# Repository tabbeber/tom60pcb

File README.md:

# Configuring PCB
To configure this PCB, head over to my [config repository](https://github.com/tabbeber/zmk-config). Follow the instructions there, and you should be set at modifying the keymap.

# About

This project is inspired by [isometria75](https://github.com/ebastler/isometria-75). 
Schematics and parts were used as a baseline, together with some information from the [nrfMicro-project](https://github.com/joric/nrfmicro/). 
Also thanks to Martin in the Norwegian mechanical keyboard discord for feedback and a slick logo to put on it.

What this project attempts to do is to fill a gap in the mid-tier of the custom mechanical keyboard market, where bluetooth/wireless boards are few and far between. 
Most of them are closed source or difficult to get hold of.
This is also mostly a project for me build skills within PCB design.
Feel free to come with any feedback - I have no clue what I'm doing.

This project was originally born out of an idea to create a PCB which was specifically made for gummyworm-mounting in regular tray mount cases without needing to massacre the poor case.
Eventually the PCB looked decent, and regular tray mount PCB would likely have a broader appeal than some hacky gummywork gasket.

# Current parts

Currently this design requires a [smaller lithium battery](https://www.aliexpress.com/item/32831998939.html), which is placed between the PCB and plate of the build.
These batteries are only 3mm tall, 30mm long and 12mm wide.
This approach is not suited for plateless builds.
Ideally uses a 2-pin JST connector, but can probably also be soldered directly to the PCB.

This PCB uses the same [Holyiot 18010](https://www.aliexpress.com/item/32868002366.html) chip that the isometria75 does. This chip comes without a bootloader, and thus need to be programmed before use.

Currently the PCB uses a forced tsangan layout for the bottom row to make space for the MCU and the battery, while the rest should be fairly universal; support for split backspace, iso and ansi.

# Current progress

Currently the project requires some more work with its footprints, but it's almost ready for prototyping. No parts are currently ordered for the future prototype.

# To-do
- [x] Make a supported layout chart
- [x] Order Battery, MCU, and Programmer for the MCU
- [x] Fix PCB and final touchups
- [x] Order PCB prototype
	* PCB rev. 0.2 has arrived
	* Current revision mostly contain cosmetic changes and improved via placements - the electrical and functional configuration remain very similar to rev. 0.2
- [x] Write and configure firmware (bootloader, ZMK)
	* ZMK firmware is functional. Currently need to figure out uploading and creating a github actions repo, as per ZMK guidelines.
- [ ] Possibly make a small wiki?

# Future possibilities

* Use of different chip(format), like the nRF52840 in the E73 format, which seem abundant on aliexpress
* Modified versions for ortho, gummyworm mount, and through-hole kits.

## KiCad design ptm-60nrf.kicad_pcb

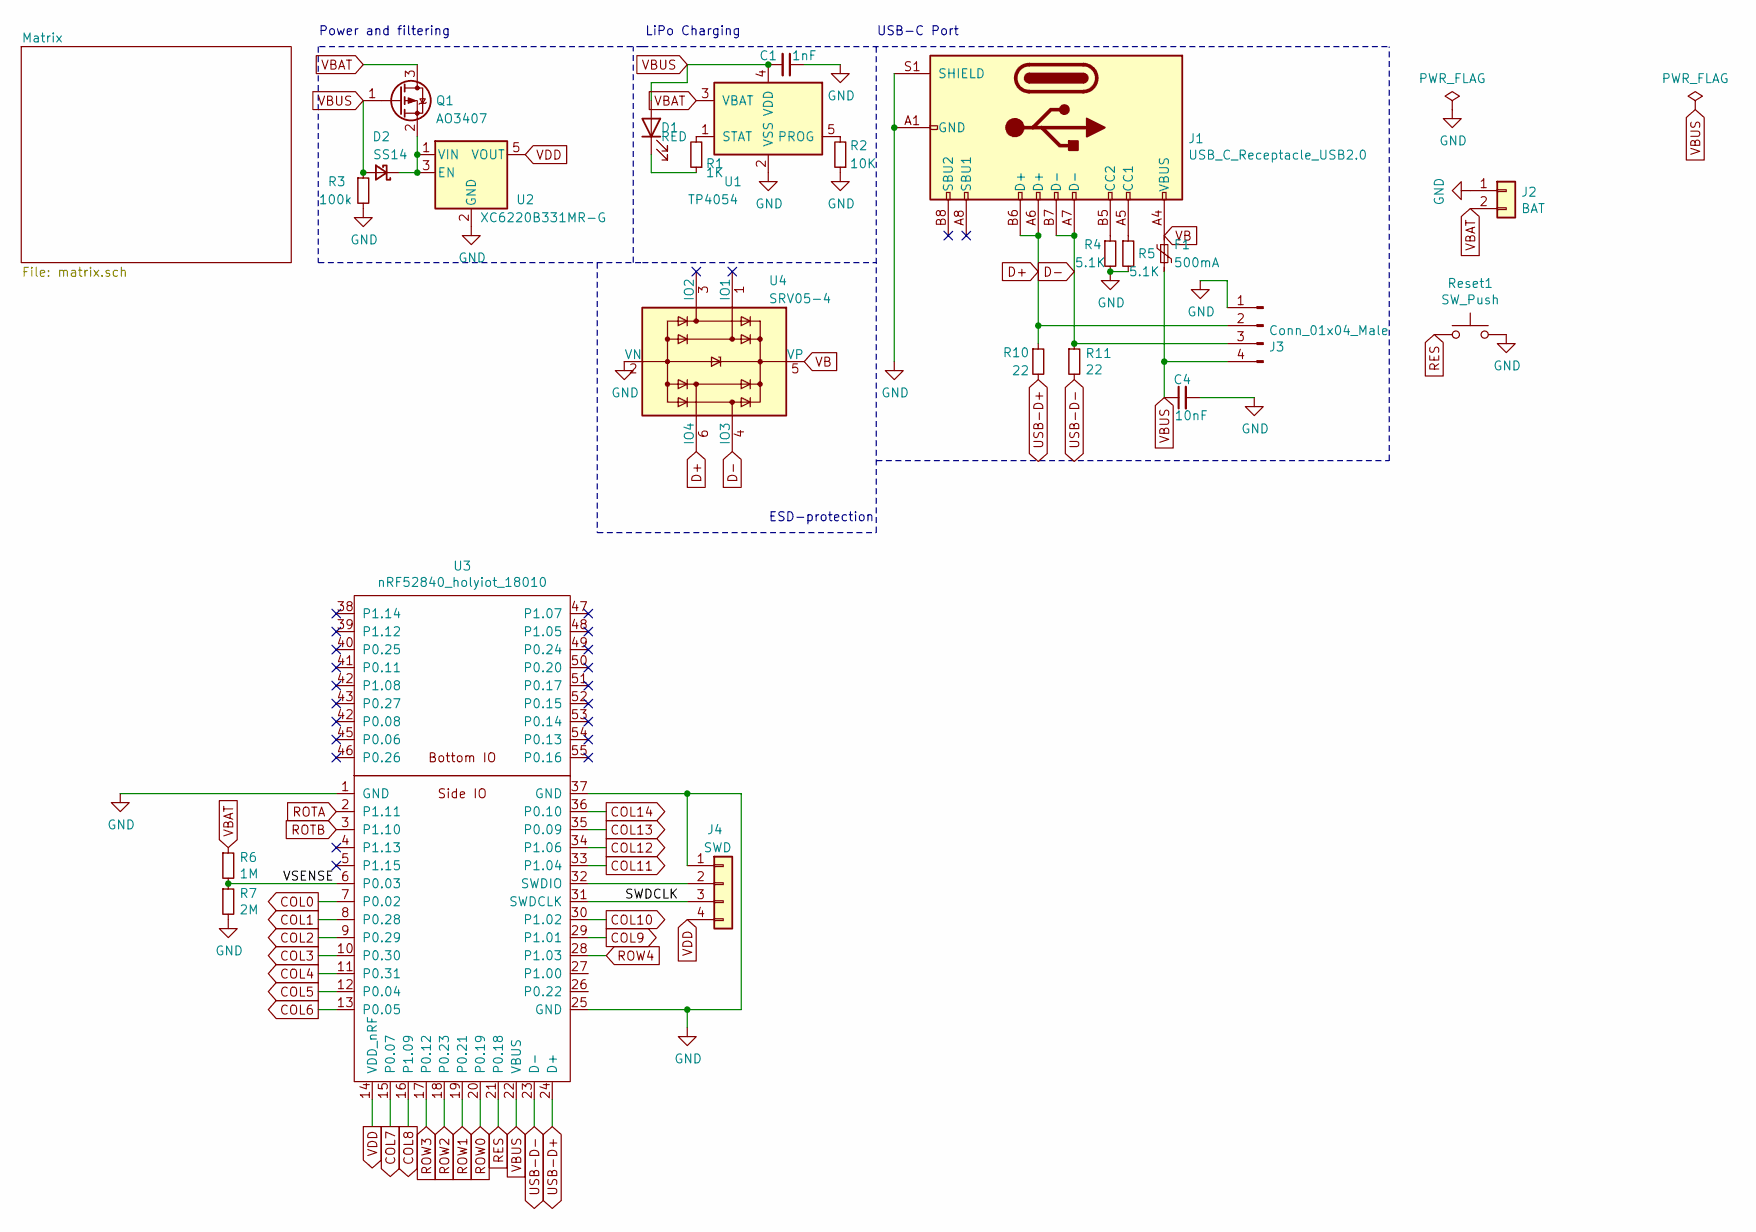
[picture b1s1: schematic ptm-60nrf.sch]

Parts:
C1: 1nF; C_0402_1005Metric; JLCPCB C1523
C4: 10nF; R_0402_1005Metric; JLCPCB C15195
D1: RED; LED_0805_2012Metric; JLCPCB C84256
D2: SS14; D_SMA; JLCPCB C2480
F1: 500mA; Fuse_1206_3216Metric; JLCPCB C70069
J1: USB_C_Receptacle_USB2.0; USB_C_Receptacle_HRO_TYPE-C-31-M-12; JLCPCB C165948
J2: BAT; JST_SH_SM02B-SRSS-TB_1x02-1MP_P1.00mm_Horizontal
J3: Conn_01x04_Male; JST_SH_BM04B-SRSS-TB_1x04-1MP_P1.00mm_Vertical
J4: SWD; PinSocket_1x04_P2.54mm_Vertical
Q1: AO3407; SOT-23; JLCPCB C181093
R1: 1K; R_0603_1608Metric; JLCPCB C21190
R2: 10K; R_0603_1608Metric; JLCPCB C25804
R3: 100k; R_0603_1608Metric; JLCPCB C25803
R4, R5: 5.1K; R_0603_1608Metric; JLCPCB C23186
R6: 1M; R_0603_1608Metric; JLCPCB C22935
R7: 2M; R_0603_1608Metric; JLCPCB C22766
R10, R11: 22; R_0603_1608Metric
Reset1: SW_Push; TestPoint_Bridge_Pitch2.0mm_Drill0.7mm
U1: TP4054; SOT-23-5; JLCPCB C32574
U2: XC6220B331MR-G; SOT-23-5; JLCPCB C86534
U3: nRF52840_holyiot_18010
U4: SRV05-4; SOT-23-6; JLCPCB C85364

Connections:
/SWDCLK: J4.3, U3.31 (SWDCLK)
/VSENSE: R6.2, R7.1, U3.6 (P0.03)
COL0: U3.7 (P0.02); also elsewhere on the board
COL1: U3.8 (P0.28); also elsewhere on the board
COL2: U3.9 (P0.29); also elsewhere on the board
COL3: U3.10 (P0.30); also elsewhere on the board
COL4: U3.11 (P0.31); also elsewhere on the board
COL5: U3.12 (P0.04); also elsewhere on the board
COL6: U3.13 (P0.05); also elsewhere on the board
COL7: U3.15 (P0.07); also elsewhere on the board
COL8: U3.16 (P1.09); also elsewhere on the board
COL9: U3.29 (P1.01); also elsewhere on the board
COL10: U3.30 (P1.02); also elsewhere on the board
COL11: U3.33 (P1.04); also elsewhere on the board
COL12: U3.34 (P1.06); also elsewhere on the board
COL13: U3.35 (P0.09); also elsewhere on the board
COL14: U3.36 (P0.10); also elsewhere on the board
D+: J1.A6 (D+), J1.B6 (D+), J3.2, R10.1, U4.6 (IO4)
D-: J1.A7 (D-), J1.B7 (D-), J3.3, R11.1, U4.4 (IO3)
GND: C1.1, C4.2, J1.A1 (GND), J1.A12 (GND), J1.B1 (GND), J1.B12 (GND), J1.S1 (SHIELD), J2.1, J3.1, J4.1, R2.1, R3.2, R4.2, R5.2, R7.2, Reset1.2, U1.2 (VSS), U2.2 (GND), U3.1 (GND), U3.25 (GND), U3.37 (GND), U4.2 (VN); also elsewhere on the board
unnamed: D1.1 (K), R1.1
unnamed: D2.1 (K), Q1.2 (S), U2.1 (VIN), U2.3 (EN)
unnamed: J1.A5 (CC1), R5.1
unnamed: J1.B5 (CC2), R4.1
unnamed: J4.2, U3.32 (SWDIO)
unnamed: R1.2, U1.1 (STAT)
unnamed: R2.2, U1.5 (PROG)
RES: Reset1.1, U3.21 (P0.18)
ROTA: U3.2 (P1.11); also elsewhere on the board
ROTB: U3.3 (P1.10); also elsewhere on the board
ROW0: U3.20 (P0.19); also elsewhere on the board
ROW1: U3.19 (P0.21); also elsewhere on the board
ROW2: U3.18 (P0.23); also elsewhere on the board
ROW3: U3.17 (P0.12); also elsewhere on the board
ROW4: U3.28 (P1.03); also elsewhere on the board
USB-D+: R10.2, U3.24 (D+)
USB-D-: R11.2, U3.23 (D-)
VB: F1.1, J1.A4 (VBUS), J1.A9 (VBUS), J1.B4 (VBUS), J1.B9 (VBUS), U4.5 (VP)
VBAT: J2.2, Q1.3 (D), R6.1, U1.3 (VBAT)
VBUS: C1.2, C4.1, D1.2 (A), D2.2 (A), F1.2, J3.4, Q1.1 (G), R3.1, U1.4 (VDD), U3.22 (VBUS)
VDD: J4.4, U2.5 (VOUT), U3.14 (VDD_nRF); also elsewhere on the board

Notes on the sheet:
Power and filtering
USB-C Port
LiPo Charging
ESD-protection

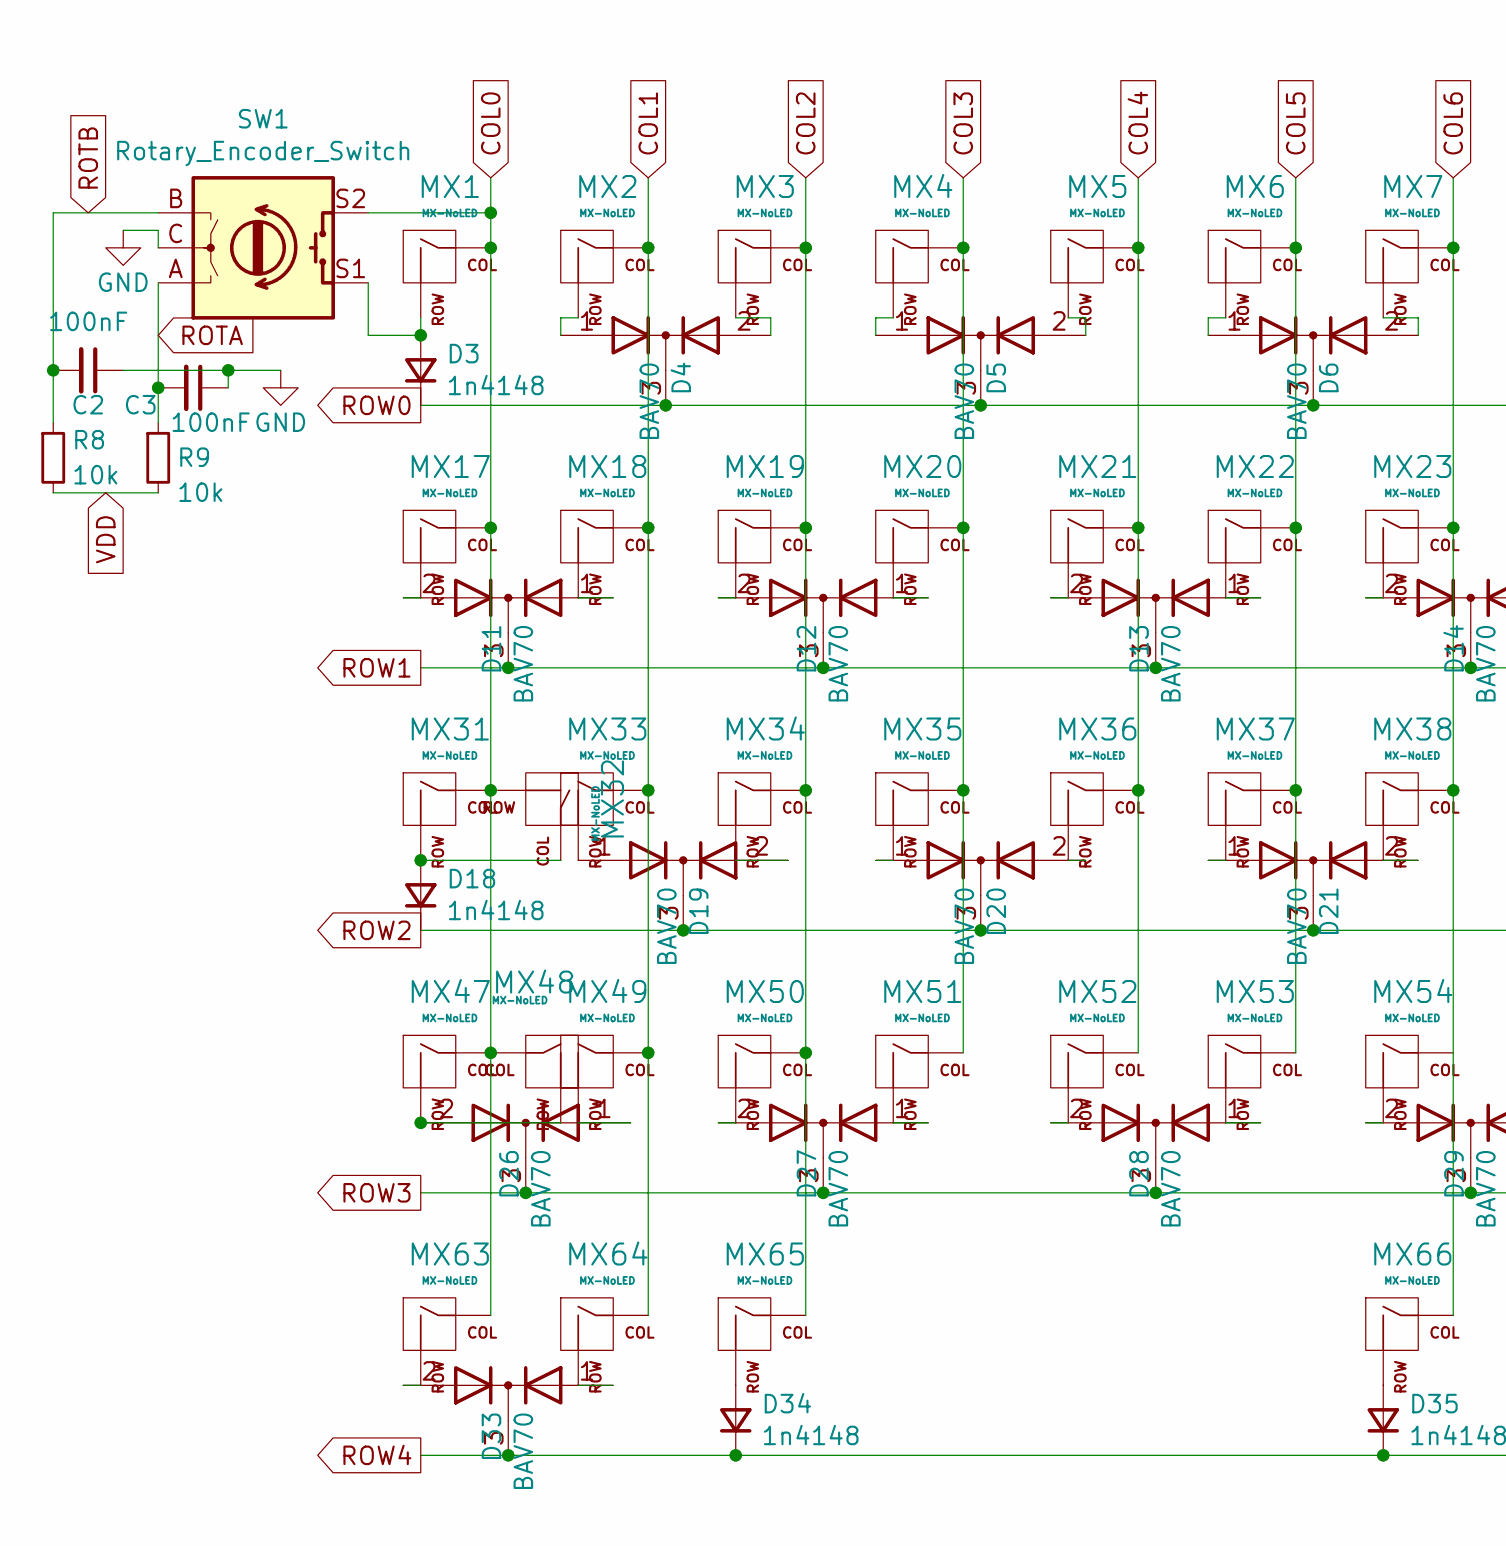
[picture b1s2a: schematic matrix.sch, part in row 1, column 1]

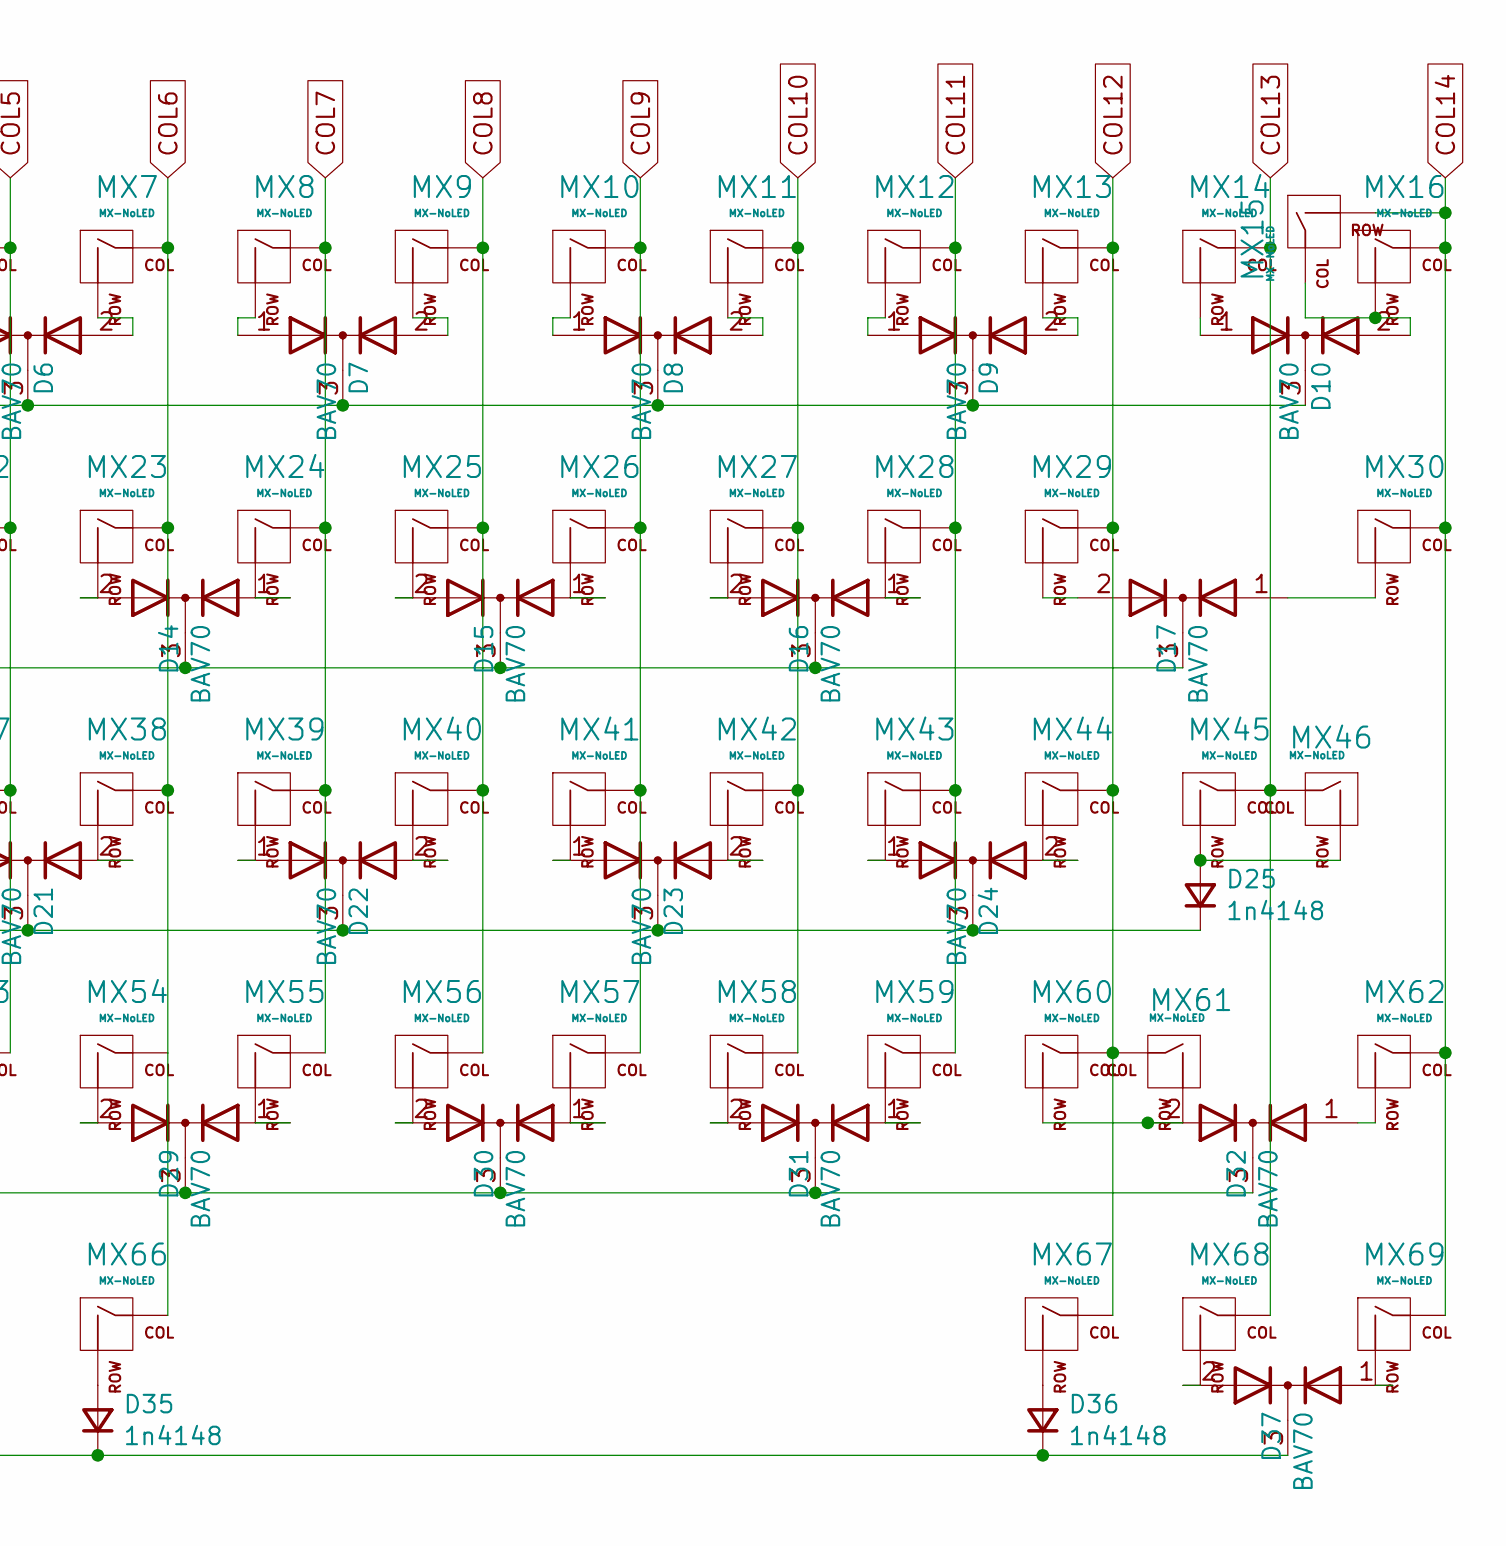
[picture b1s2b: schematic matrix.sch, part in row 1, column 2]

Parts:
C2, C3: 100nF; C_0402_1005Metric; JLCPCB C1525
D3, D18, D25, D34, D35, D36: 1n4148; D_SOD-323F; JLCPCB C2128
D4, D5, D6, D7, D8, D9, D10, D11, D12, D13, D14, D15, D16, D17, D19, D20, D21, D22, D23, D24, D26, D27, D28, D29, D30, D31, D32, D33, D37: BAV70; SOT-23; JLCPCB C68978
MX1, MX2, MX3, MX4, MX5, MX6, MX7, MX8, MX9, MX10, MX11, MX12, MX13, MX14, MX16, MX18, MX19, MX20, MX21, MX22, MX23, MX24, MX25, MX26, MX27, MX28, MX29, MX33, MX34, MX35, MX36, MX37, MX38, MX39, MX40, MX41, MX42, MX43, MX44, MX49, MX50, MX51, MX52, MX53, MX54, MX55, MX56, MX57, MX58, MX59, MX62, MX64, MX68: MX-NoLED; MXOnly-1U-NoLED
MX15: MX-NoLED; MXOnly-2U-NoLED
MX17, MX30, MX63, MX65, MX67, MX69: MX-NoLED; MXOnly-1.5U-NoLED
MX31, MX47: MX-NoLED; MXOnly-1.25U-NoLED
MX32, MX60: MX-NoLED; MXOnly-1.75U-NoLED
MX45, MX48: MX-NoLED; MXOnly-2.25U-NoLED
MX46: MX-NoLED; MXOnly-ISO-ReversedStabilizers
MX61: MX-NoLED; MXOnly-2.75U-NoLED
MX66: MX-NoLED; MXOnly-7U-ReversedStabilizers-NoLED
R8, R9: 10k; R_0603_1608Metric; JLCPCB C25804
SW1: Rotary_Encoder_Switch; RotaryEncoder_Alps_EC11E-Switch_Vertical_H20mm

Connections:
COL0: MX1.1 (COL), MX17.1 (COL), MX31.1 (COL), MX32.2 (ROW), MX47.1 (COL), MX48.1 (COL), MX63.1 (COL), SW1.S2; also elsewhere on the board
COL1: MX2.1 (COL), MX18.1 (COL), MX33.1 (COL), MX49.1 (COL), MX64.1 (COL); also elsewhere on the board
COL2: MX3.1 (COL), MX19.1 (COL), MX34.1 (COL), MX50.1 (COL), MX65.1 (COL); also elsewhere on the board
COL3: MX4.1 (COL), MX20.1 (COL), MX35.1 (COL), MX51.1 (COL); also elsewhere on the board
COL4: MX5.1 (COL), MX21.1 (COL), MX36.1 (COL), MX52.1 (COL); also elsewhere on the board
COL5: MX6.1 (COL), MX22.1 (COL), MX37.1 (COL), MX53.1 (COL); also elsewhere on the board
COL6: MX7.1 (COL), MX23.1 (COL), MX38.1 (COL), MX54.1 (COL), MX66.1 (COL); also elsewhere on the board
COL7: MX8.1 (COL), MX24.1 (COL), MX39.1 (COL), MX55.1 (COL); also elsewhere on the board
COL8: MX9.1 (COL), MX25.1 (COL), MX40.1 (COL), MX56.1 (COL); also elsewhere on the board
COL9: MX10.1 (COL), MX26.1 (COL), MX41.1 (COL), MX57.1 (COL); also elsewhere on the board
COL10: MX11.1 (COL), MX27.1 (COL), MX42.1 (COL), MX58.1 (COL); also elsewhere on the board
COL11: MX12.1 (COL), MX28.1 (COL), MX43.1 (COL), MX59.1 (COL); also elsewhere on the board
COL12: MX13.1 (COL), MX29.1 (COL), MX44.1 (COL), MX60.1 (COL), MX61.1 (COL), MX67.1 (COL); also elsewhere on the board
COL13: MX14.1 (COL), MX45.1 (COL), MX46.1 (COL), MX68.1 (COL); also elsewhere on the board
COL14: MX15.2 (ROW), MX16.1 (COL), MX30.1 (COL), MX62.1 (COL), MX69.1 (COL); also elsewhere on the board
GND: C2.1, C3.1, SW1.C; also elsewhere on the board
unnamed: D3.2 (A), MX1.2 (ROW), SW1.S1
unnamed: D4.1 (A), MX2.2 (ROW)
unnamed: D4.2 (A), MX3.2 (ROW)
unnamed: D5.1 (A), MX4.2 (ROW)
unnamed: D5.2 (A), MX5.2 (ROW)
unnamed: D6.1 (A), MX6.2 (ROW)
unnamed: D6.2 (A), MX7.2 (ROW)
unnamed: D7.1 (A), MX8.2 (ROW)
unnamed: D7.2 (A), MX9.2 (ROW)
unnamed: D8.1 (A), MX10.2 (ROW)
unnamed: D8.2 (A), MX11.2 (ROW)
unnamed: D9.1 (A), MX12.2 (ROW)
unnamed: D9.2 (A), MX13.2 (ROW)
unnamed: D10.1 (A), MX14.2 (ROW)
unnamed: D10.2 (A), MX15.1 (COL), MX16.2 (ROW)
unnamed: D11.1 (A), MX18.2 (ROW)
unnamed: D11.2 (A), MX17.2 (ROW)
unnamed: D12.1 (A), MX20.2 (ROW)
unnamed: D12.2 (A), MX19.2 (ROW)
unnamed: D13.1 (A), MX22.2 (ROW)
unnamed: D13.2 (A), MX21.2 (ROW)
unnamed: D14.1 (A), MX24.2 (ROW)
unnamed: D14.2 (A), MX23.2 (ROW)
unnamed: D15.1 (A), MX26.2 (ROW)
unnamed: D15.2 (A), MX25.2 (ROW)
unnamed: D16.1 (A), MX28.2 (ROW)
unnamed: D16.2 (A), MX27.2 (ROW)
unnamed: D17.1 (A), MX30.2 (ROW)
unnamed: D17.2 (A), MX29.2 (ROW)
unnamed: D18.2 (A), MX31.2 (ROW), MX32.1 (COL)
unnamed: D19.1 (A), MX33.2 (ROW)
unnamed: D19.2 (A), MX34.2 (ROW)
unnamed: D20.1 (A), MX35.2 (ROW)
unnamed: D20.2 (A), MX36.2 (ROW)
unnamed: D21.1 (A), MX37.2 (ROW)
unnamed: D21.2 (A), MX38.2 (ROW)
unnamed: D22.1 (A), MX39.2 (ROW)
unnamed: D22.2 (A), MX40.2 (ROW)
unnamed: D23.1 (A), MX41.2 (ROW)
unnamed: D23.2 (A), MX42.2 (ROW)
unnamed: D24.1 (A), MX43.2 (ROW)
unnamed: D24.2 (A), MX44.2 (ROW)
unnamed: D25.2 (A), MX45.2 (ROW), MX46.2 (ROW)
unnamed: D26.1 (A), MX49.2 (ROW)
unnamed: D26.2 (A), MX47.2 (ROW), MX48.2 (ROW)
unnamed: D27.1 (A), MX51.2 (ROW)
unnamed: D27.2 (A), MX50.2 (ROW)
unnamed: D28.1 (A), MX53.2 (ROW)
unnamed: D28.2 (A), MX52.2 (ROW)
unnamed: D29.1 (A), MX55.2 (ROW)
unnamed: D29.2 (A), MX54.2 (ROW)
unnamed: D30.1 (A), MX57.2 (ROW)
unnamed: D30.2 (A), MX56.2 (ROW)
unnamed: D31.1 (A), MX59.2 (ROW)
unnamed: D31.2 (A), MX58.2 (ROW)
unnamed: D32.1 (A), MX62.2 (ROW)
unnamed: D32.2 (A), MX60.2 (ROW), MX61.2 (ROW)
unnamed: D33.1 (A), MX64.2 (ROW)
unnamed: D33.2 (A), MX63.2 (ROW)
unnamed: D34.2 (A), MX65.2 (ROW)
unnamed: D35.2 (A), MX66.2 (ROW)
unnamed: D36.2 (A), MX67.2 (ROW)
unnamed: D37.1 (A), MX69.2 (ROW)
unnamed: D37.2 (A), MX68.2 (ROW)
ROTA: C3.2, R9.1, SW1.A; also elsewhere on the board
ROTB: C2.2, R8.1, SW1.B; also elsewhere on the board
ROW0: D3.1 (K), D4.3 (K), D5.3 (K), D6.3 (K), D7.3 (K), D8.3 (K), D9.3 (K), D10.3 (K); also elsewhere on the board
ROW1: D11.3 (K), D12.3 (K), D13.3 (K), D14.3 (K), D15.3 (K), D16.3 (K), D17.3 (K); also elsewhere on the board
ROW2: D18.1 (K), D19.3 (K), D20.3 (K), D21.3 (K), D22.3 (K), D23.3 (K), D24.3 (K), D25.1 (K); also elsewhere on the board
ROW3: D26.3 (K), D27.3 (K), D28.3 (K), D29.3 (K), D30.3 (K), D31.3 (K), D32.3 (K); also elsewhere on the board
ROW4: D33.3 (K), D34.1 (K), D35.1 (K), D36.1 (K), D37.3 (K); also elsewhere on the board
VDD: R8.2, R9.2; also elsewhere on the board

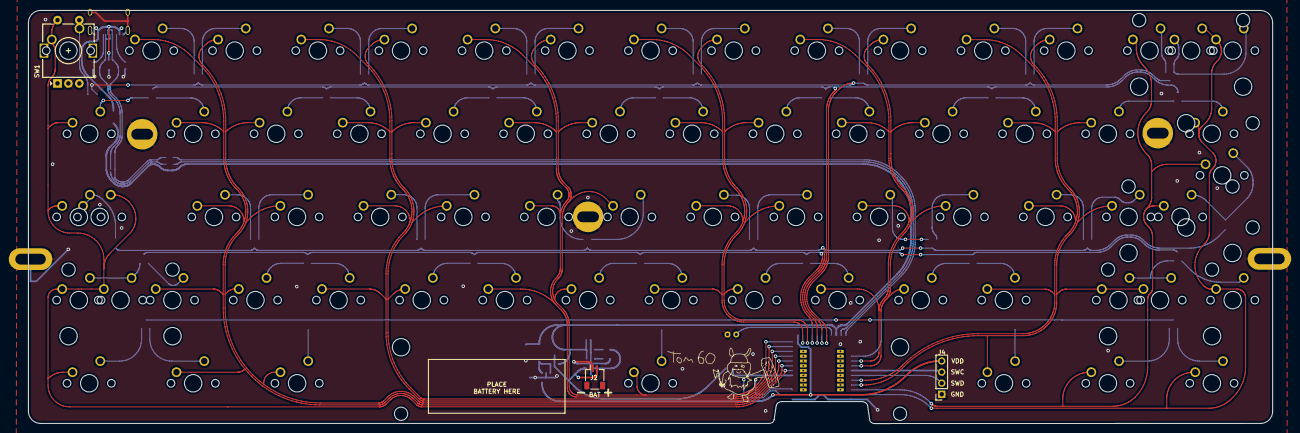
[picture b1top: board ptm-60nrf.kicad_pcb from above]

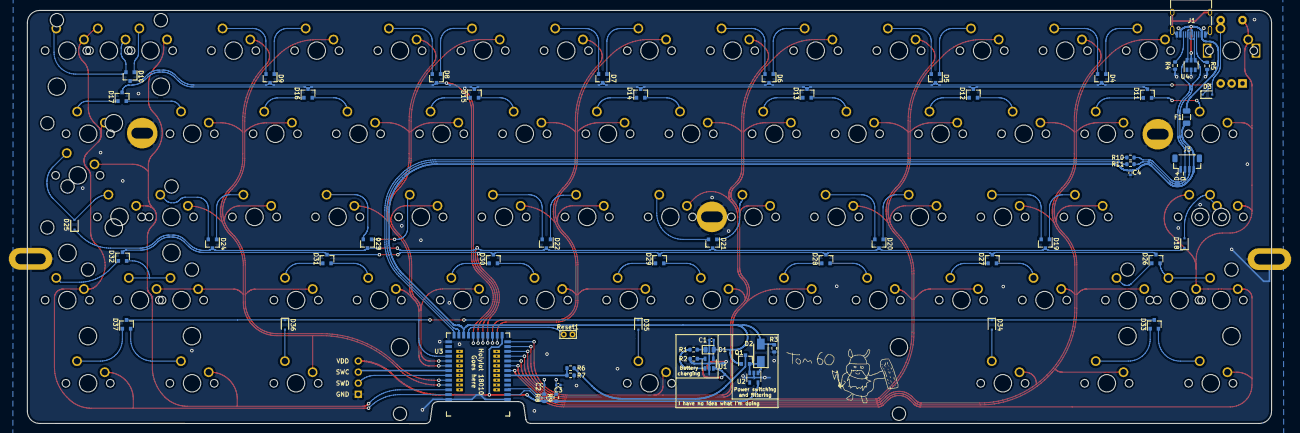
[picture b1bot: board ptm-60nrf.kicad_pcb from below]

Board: 2 copper layers, 285.0 x 94.6 mm, 138 parts (61 on the bottom side), 105 nets.

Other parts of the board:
HOLE: VAL**; PKRHSL
HOLE#2, HOLE#3, HOLE#4: VAL**; PKRH
HOLE#5: VAL**; PKRHSL

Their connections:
GND: HOLE.1, HOLE#2.1, HOLE#3.1, HOLE#4.1, HOLE#5.1; also elsewhere on the board

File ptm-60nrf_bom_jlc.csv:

"Comment","Designator","Footprint","LCSC Part #"
"1nF","C1","C_0402_1005Metric","C1523"
"100nF","C2,C3","C_0402_1005Metric","C1525"
"10nF","C4","R_0402_1005Metric","C15195"
"RED","D1","LED_0805_2012Metric","C84256"
"SS14","D2","D_SMA","C2480"
"BAV70","D4,D5,D6,D7,D8,D9,D10,D11,D12,D13,D14,D15,D16,D17,D19,D20,D21,D22,D23,D24,D26,D27,D28,D29,D30,D31,D32,D37,D33","SOT-23","C68978"
"1n4148","D18,D25,D34,D35,D36,D3","D_SOD-323F","C2128"
"500mA","F1","Fuse_1206_3216Metric","C70069"
"USB_C_Receptacle_USB2.0","J1","USB_C_Receptacle_HRO_TYPE-C-31-M-12","C165948"
"AO3407","Q1","SOT-23","C181093"
"1K","R1","R_0603_1608Metric","C21190"
"10K","R2","R_0603_1608Metric","C25804"
"100k","R3","R_0603_1608Metric","C25803"
"5.1K","R4,R5","R_0603_1608Metric","C23186"
"1M","R6","R_0603_1608Metric","C22935"
"2M","R7","R_0603_1608Metric","C22766"
"10k","R9,R8","R_0603_1608Metric","C25804"
"TP4054","U1","SOT-23-5","C32574"
"XC6220B331MR-G","U2","SOT-23-5","C86534"
"SRV05-4","U4","SOT-23-6","C85364"

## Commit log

2021-05-31 initialise git repo for wireless 60% keyboard
2021-05-31 added readme
2021-05-31 new update pls halp
2021-05-31 added images
2021-05-31 add to-do list
2021-05-31 errata and deletion of backup files
2021-05-31 added gerbers
2021-05-31 added license
2021-05-31 added img folder for some structure
2021-05-31 fixed issues with USB tracing, grounded mounting holes and added gitignore
2021-06-01 further changes - added copper pour, some cosmetic fixes, and changes to readme
2021-06-01 added kle layout scheme for pcb
2021-06-01 actually add the image
2021-06-01 update README to reflect recent changes
2021-06-01 cosmetic changes
2021-06-01 Further improvements, moved some traces away from mounting holes
2021-06-01 swapped reset button
2021-06-01 fixed an upside down spacebar footprint
2021-06-01 added some more eyecandy and fixed typos
2021-06-02 fixed schematic flaws and caps lock (thanks Martin!)
2021-06-02 added hole for antenna
2021-06-02 increased distance between cut and antenna hole
2021-06-02 further move traces away from cuts
2021-06-02 minor fixes
2021-06-02 restored lost artwork
2021-06-02 fixed images
2021-06-02 squashed bugs in schematic and rewired pwr/chrg
2021-06-02 cosmetic changes and thicker traces in power block
2021-06-02 cosmetic changes and removal of gnd in usb bus
2021-06-03 some cosmetic changes - might revert some
2021-06-03 cosmetic adjustments
2021-06-03 further cosmetic adjustments
2021-06-03 further beautification
2021-06-03 further improvements
2021-06-03 created branch 0.2 for alternate mcu location. Heavy cleanup
2021-06-04 updated branch and ordered pcb prototype
2021-06-04 merged v0.2 into main
2021-06-04 updated images
2021-06-04 cosmetic improvements of a major degree - v0.3
2021-06-06 improved parts placements and silkscreen text (jlc compatible)
2021-06-07 modified to use BAV70 diodes
2021-06-07 added images using BAV70 diodes
2021-06-07 rounding of traces
2021-06-08 further changes
2021-06-08 improved symmetry
2021-06-08 discovered a way to copy and paste traces reliably
2021-06-08 further corner smoothing
2021-06-08 prototype pcb en route, readme reflecting that
2021-06-09 added footprint for rotary encoder on esc - renamed v0.4
2021-06-12 added support for daughterboard (jst footprint)
2021-06-16 swapped switch to pads (savings), added resistor to data
2021-12-20 swapped polarity on battery connector… Other minor fixes
2021-12-20 Update LICENSE
2021-12-26 changing encoder traces
2021-12-29 moved MCU in order to properly support Tofu and Mekanisk with addition standoffs
2022-01-01 moved traces, fixed curves
2022-01-01 fixed a trace
